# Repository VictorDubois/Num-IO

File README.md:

# Num-IO

Mesa compatible SPI daughter board aimed at being a drop-in remplacement for a 32I/24O Num 1060 board
Also featuring an expansion port with 4 isoSPI lines for panel connectivity

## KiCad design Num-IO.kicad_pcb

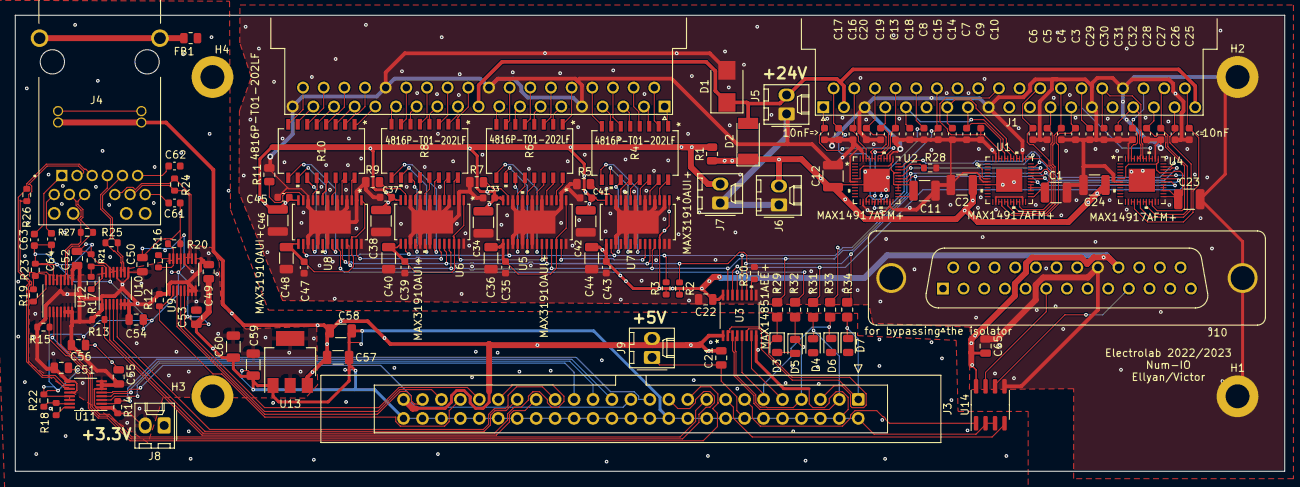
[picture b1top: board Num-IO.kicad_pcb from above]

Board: 4 copper layers, 170.2 x 61.1 mm, 135 parts (0 on the bottom side), 165 nets.

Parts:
C1, C11, C23: 1uF; C_1210_3225Metric
C2, C12, C24: 10uF; C_1210_3225Metric
C3, C4, C5, C6, C7, C8, C9, C10, C13, C14, C15, C16, C17, C18, C19, C20, C25, C26, C27, C28, C29, C30, C31, C32: 10nF; C_0603_1608Metric
C21, C22, C65: 0.1uF; C_0805_2012Metric
C33, C37, C41, C45: 100nF 100V ceramic; C_0603_1608Metric
C34, C38, C42, C46: 10uF 60V ceramic; C_1210_3225Metric
C35, C39, C43, C47: 100nF 10V C; C_0603_1608Metric
C36, C40, C44, C48: 4.7uF 10V lowESR; C_1206_3216Metric
C49, C50, C51, C52, C53, C54, C55, C56: 100nF; C_0805_2012Metric
C57, C58, C59, C60: 10uF; C_1206_3216Metric
C61, C62, C63, C64: <27pF; C_0603_1608Metric
D1: SM6T36A; D_SMB
D2: 1N4007; D_MELF
D3, D4, D5, D6, D7: BZY55B5V6 RBG; D_0805_2012Metric
FB1: FerriteBead; R_0805_2012Metric
H1, H2, H3, H4: MountingHole_Pad; MountingHole_3.2mm_M3_DIN965_Pad
J1: DB37_Female; DSUB-37_Female_Horizontal_P2.77x2.54mm_EdgePinOffset9.40mm
J2: DB37_Male; DSUB-37_Male_Horizontal_P2.77x2.54mm_EdgePinOffset9.40mm
J3: Conn_02x25_Odd_Even; IDC-Header_2x25_P2.54mm_Latch_Vertical
J4: 0826-1X1T-GH-F; BEL_0826-1X1T-GH-F
J5, J6, J7, J8, J9: Conn_01x02_Male; Molex_KK-254_AE-6410-02A_1x02_P2.54mm_Vertical
J10: DB25_Female; DSUB-25_Female_Vertical_P2.77x2.84mm_MountingHoles
R1: 150R; R_0805_2012Metric
R2, R3, R30: 3.3k; R_0603_1608Metric
R4, R6, R8, R10: 4816P-T01-202LF; 4816P
R5, R7, R9, R11: 15k; R_0805_2012Metric
R12, R13, R14, R15: 2kR; R_0603_1608Metric
R16, R17, R18, R19: 2.8kR; R_0603_1608Metric
R20, R21, R22, R23: 1.21kR; R_0603_1608Metric
R24, R25, R26, R27: 120R; R_0603_1608Metric
R28: 100k; R_0603_1608Metric
R29, R31, R32, R33, R34: NC; R_0805_2012Metric_Pad1.20x1.40mm_HandSolder
U1, U2, U4: MAX14917AFM+; MAX14917AFM&plus_
U3: MAX14851AEE+; MAX14851AEE&plus_
U5, U6, U7, U8: MAX31910AUI+; MAX31910AUI&plus_
U9, U10, U11, U12: LTC6820HMS; MSOP-16_3x4.039mm_P0.5mm
U13: AP1117-33; SOT-223-3_TabPin2
U14: HCPL-063A; SOIC-8_3.9x4.9mm_P1.27mm

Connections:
+3V3: C49.1, C50.1, C51.1, C52.1, C53.1, C54.1, C55.1, C56.1, C59.1, C60.1, J8.2, R12.1, R13.1, R14.1, R15.1, U9.1 (EN), U9.6 (VDDS), U9.7 (POL), U9.8 (PHA), U9.9 (VDD), U9.12 (MSTR), U10.1 (EN), U10.6 (VDDS), U10.7 (POL), U10.8 (PHA), U10.9 (VDD), U10.12 (MSTR), U11.1 (EN), U11.6 (VDDS), U11.7 (POL), U11.8 (PHA), U11.9 (VDD), U11.12 (MSTR), U12.1 (EN), U12.6 (VDDS), U12.7 (POL), U12.8 (PHA), U12.9 (VDD), U12.12 (MSTR), U13.2 (VO)
+5VD: C21.2, C57.1, C58.1, J3.49, J4.13 (VC1), J4.14 (VC2), J9.2, U3.1 (VCCA), U13.3 (VI)
+24V: D1.1 (A1), D2.2 (A), J1.2, J1.19, J2.10, J5.2
/*FAULT: R3.2, R33.2, U1.35 (*FAULT), U2.35 (*FAULT), U3.12 (INB2), U4.35 (*FAULT), U5.16 (*FAULT), U6.16 (*FAULT), U7.16 (*FAULT), U8.16 (*FAULT)
/CLK: R29.2, U1.31 (CLK), U2.31 (CLK), U3.15 (OUTB1), U4.31 (CLK), U5.25 (CLK), U6.25 (CLK), U7.25 (CLK), U8.25 (CLK)
/CS: R2.1, R34.2, U1.30 (*CS), U2.30 (*CS), U3.11 (I/OB1), U4.30 (*CS), U5.24 (*CS), U6.24 (*CS), U7.24 (*CS), U8.24 (*CS)
/FPGA Connector/SPI0.*CS: D7.1 (A1), J3.1, R34.1, U3.6 (I/OA1)
/FPGA Connector/SPI0.CLK: D3.1 (A1), J3.5, R29.1, U3.2 (INA1)
/FPGA Connector/SPI0.SDI: D4.1 (A1), J3.3, R31.1, U3.3 (INA2)
/FPGA Connector/SPI0.SDO: D5.1 (A1), J3.7, R32.1, U3.4 (OUTA1)
/FPGA Connector/SPI1.*CS: J3.17, U12.5 (*CS)
/FPGA Connector/SPI1.CLK: J3.21, U12.4 (SCK)
/FPGA Connector/SPI1.SDI: J3.19, R15.2, U12.2 (MOSI)
/FPGA Connector/SPI1.SDO: J3.23, U12.3 (MISO)
/FPGA Connector/SPI2.*CS: J3.25, U11.5 (*CS)
/FPGA Connector/SPI2.CLK: J3.29, U11.4 (SCK)
/FPGA Connector/SPI2.SDI: J3.27, R14.2, U11.2 (MOSI)
/FPGA Connector/SPI2.SDO: J3.31, U11.3 (MISO)
/FPGA Connector/SPI3.*CS: J3.33, U10.5 (*CS)
/FPGA Connector/SPI3.CLK: J3.37, U10.4 (SCK)
/FPGA Connector/SPI3.SDI: J3.35, R13.2, U10.2 (MOSI)
/FPGA Connector/SPI3.SDO: J3.39, U10.3 (MISO)
/FPGA Connector/SPI4.*CS: J3.41, U9.5 (*CS)
/FPGA Connector/SPI4.CLK: J3.45, U9.4 (SCK)
/FPGA Connector/SPI4.SDI: J3.43, R12.2, U9.2 (MOSI)
/FPGA Connector/SPI4.SDO: J3.47, U9.3 (MISO)
/I*FAULT: D6.1 (A1), J3.11, R33.1, U3.5 (OUTA2)
/IADDR: J3.9, U3.7 (I/OA2)
/IMPGA: J3.13, U14.1 (A1)
/IMPGB: J3.15, U14.4 (A2)
/Input connector/IN1: J2.1, R4.1
/Input connector/IN2: J2.20, R4.2
/Input connector/IN3: J2.2, R4.3
/Input connector/IN4: J2.21, R4.4
/Input connector/IN5: J2.3, R4.5
/Input connector/IN6: J2.22, R4.6
/Input connector/IN7: J2.4, R4.7
/Input connector/IN8: J2.23, R4.8
/Input connector/IN9: J2.24, R6.1
/Input connector/IN10: J2.6, R6.2
/Input connector/IN11: J2.25, R6.3
/Input connector/IN12: J2.7, R6.4
/Input connector/IN13: J2.26, R6.5
/Input connector/IN14: J2.8, R6.6
/Input connector/IN15: J2.27, R6.7
/Input connector/IN16: J2.9, R6.8
/Input connector/IN17: J2.29, R8.1
/Input connector/IN18: J2.11, R8.2
/Input connector/IN19: J2.30, R8.3
/Input connector/IN20: J2.12, R8.4
/Input connector/IN21: J2.31, R8.5
/Input connector/IN22: J2.13, R8.6
/Input connector/IN23: J2.32, R8.7
/Input connector/IN24: J2.14, R8.8
/Input connector/IN25: J2.15, R10.1
/Input connector/IN26: J2.34, R10.2
/Input connector/IN27: J2.16, R10.3
/Input connector/IN28: J2.35, R10.4
/Input connector/IN29: J2.17, R10.5
/Input connector/IN30: J2.36, R10.6
/Input connector/IN31: J2.18, R10.7
/Input connector/IN32: J2.37, R10.8
/IsoPWR: C22.1, C43.1, C44.1, C65.2, J10.22, R2.2, R3.1, U3.16 (VCCB), U7.1 (DB0), U7.15 (5VOUT), U7.26 (MODESEL), U14.8 (VCC)
/MPG/MPGA: J10.6, U14.7 (VO1)
/MPG/MPGB: J10.10, U14.6 (VO2)
/RJ45 extension/TRD1+: J4.11 (TRD1+), R24.1, U9.11 (IP)
/RJ45 extension/TRD1-: J4.10 (TRD1-), R24.2, U9.10 (IM)
/RJ45 extension/TRD2+: J4.4 (TRD2+), R25.1, U10.11 (IP)
/RJ45 extension/TRD2-: J4.5 (TRD2-), R25.2, U10.10 (IM)
/RJ45 extension/TRD3+: J4.3 (TRD3+), R26.1, U11.11 (IP)
/RJ45 extension/TRD3-: J4.2 (TRD3-), R26.2, U11.10 (IM)
/RJ45 extension/TRD4+: J4.8 (TRD4+), R27.1, U12.11 (IP)
/RJ45 extension/TRD4-: J4.9 (TRD4-), R27.2, U12.10 (IM)
/SDI: R31.2, U3.14 (OUTB2), U4.32 (SDI)
/SDO: R32.2, U3.13 (INB1), U8.23 (SOUT)
/input channel 1-8/SDO: U5.27 (SIN), U7.23 (SOUT)
/input channel 9-16/5VOUT: C35.1, C36.1, U5.1 (DB0), U5.15 (5VOUT), U5.26 (MODESEL)
/input channel 17-24/5VOUT: C39.1, C40.1, U6.1 (DB0), U6.15 (5VOUT), U6.26 (MODESEL)
/input channel 17-24/SDI: U5.23 (SOUT), U6.27 (SIN)
/input channel 17-24/SDO: U6.23 (SOUT), U8.27 (SIN)
/input channel 25-32/5VOUT: C47.1, C48.1, U8.1 (DB0), U8.15 (5VOUT), U8.26 (MODESEL)
/output channel 1-8/OUT1: C25.1, J1.37, U4.15 (OUT1), U4.16 (OUT1)
/output channel 1-8/OUT2: C26.1, J1.18, U4.17 (OUT2), U4.18 (OUT2)
/output channel 1-8/OUT3: C27.1, J1.36, U4.19 (OUT3), U4.20 (OUT3)
/output channel 1-8/OUT4: C28.1, J1.17, U4.21 (OUT4), U4.22 (OUT4)
/output channel 1-8/OUT5: C32.1, J1.35, U4.45 (OUT5), U4.46 (OUT5)
/output channel 1-8/OUT6: C31.1, J1.16, U4.43 (OUT6), U4.44 (OUT6)
/output channel 1-8/OUT7: C30.1, J1.33, U4.41 (OUT7), U4.42 (OUT7)
/output channel 1-8/OUT8: C29.1, J1.32, U4.39 (OUT8), U4.40 (OUT8)
/output channel 1-8/SDO: U1.32 (SDI), U4.34 (SDO)
/output channel 1-8/VL: C23.1, U4.6 (VL), U4.25 (CRCEN), U4.27 (SPIWD), U4.28 (EN), U4.29 (VA), U4.33 (SYNCH), U4.37 (VL)
/output channel 9-16/OUT1: C3.1, J1.13, U1.15 (OUT1), U1.16 (OUT1)
/output channel 9-16/OUT2: C4.1, J1.31, U1.17 (OUT2), U1.18 (OUT2)
/output channel 9-16/OUT3: C5.1, J1.12, U1.19 (OUT3), U1.20 (OUT3)
/output channel 9-16/OUT4: C6.1, J1.30, U1.21 (OUT4), U1.22 (OUT4)
/output channel 9-16/OUT5: C10.1, J1.28, U1.45 (OUT5), U1.46 (OUT5)
/output channel 9-16/OUT6: C9.1, J1.8, U1.43 (OUT6), U1.44 (OUT6)
/output channel 9-16/OUT7: C8.1, J1.5, U1.41 (OUT7), U1.42 (OUT7)
/output channel 9-16/OUT8: C7.1, J1.7, U1.39 (OUT8), U1.40 (OUT8)
/output channel 9-16/VL: C1.1, U1.6 (VL), U1.25 (CRCEN), U1.27 (SPIWD), U1.28 (EN), U1.29 (VA), U1.33 (SYNCH), U1.37 (VL)
/output channel 17-24/OUT1: C13.1, J1.4, U2.15 (OUT1), U2.16 (OUT1)
/output channel 17-24/OUT2: C14.1, J1.25, U2.17 (OUT2), U2.18 (OUT2)
/output channel 17-24/OUT3: C15.1, J1.24, U2.19 (OUT3), U2.20 (OUT3)
/output channel 17-24/OUT4: C16.1, J1.20, U2.21 (OUT4), U2.22 (OUT4)
/output channel 17-24/OUT5: C20.1, J1.21, U2.45 (OUT5), U2.46 (OUT5)
/output channel 17-24/OUT6: C19.1, J1.22, U2.43 (OUT6), U2.44 (OUT6)
/output channel 17-24/OUT7: C18.1, J1.23, U2.41 (OUT7), U2.42 (OUT7)
/output channel 17-24/OUT8: C17.1, J1.1, U2.39 (OUT8), U2.40 (OUT8)
/output channel 17-24/SDI: U1.34 (SDO), U2.32 (SDI)
/output channel 17-24/SDO: R28.2, U2.34 (SDO)
/output channel 17-24/VL: C11.1, U2.6 (VL), U2.25 (CRCEN), U2.27 (SPIWD), U2.28 (EN), U2.29 (VA), U2.33 (SYNCH), U2.37 (VL)
GNDD: C21.1, C49.2, C50.2, C51.2, C52.2, C53.2, C54.2, C55.2, C56.2, C57.2, C58.2, C59.2, C60.2, C61.1, C62.1, C63.1, C64.1, D3.2 (A2), D4.2 (A2), D5.2 (A2), D6.2 (A2), D7.2 (A2), FB1.1, J3.2, J3.4, J3.6, J3.8, J3.10, J3.12, J3.14, J3.16, J3.18, J3.20, J3.22, J3.24, J3.26, J3.28, J3.30, J3.32, J3.34, J3.36, J3.38, J3.40, J3.42, J3.44, J3.46, J3.48, J3.50, J4.15 (VC3), J4.16 (VC4), J8.1, J9.1, R20.2, R21.2, R22.2, R23.2, U3.8 (GNDA), U9.13 (SLOW), U9.14 (GND), U10.13 (SLOW), U10.14 (GND), U11.13 (SLOW), U11.14 (GND), U12.13 (SLOW), U12.14 (GND), U13.1 (GND), U14.2 (C1), U14.3 (C2)
GNDPWR: C1.2, C2.2, C3.2, C4.2, C5.2, C6.2, C7.2, C8.2, C9.2, C10.2, C11.2, C12.2, C13.2, C14.2, C15.2, C16.2, C17.2, C18.2, C19.2, C20.2, C22.2, C23.2, C24.2, C25.2, C26.2, C27.2, C28.2, C29.2, C30.2, C31.2, C32.2, C33.2, C34.2, C35.2, C36.2, C37.2, C38.2, C39.2, C40.2, C41.2, C42.2, C43.2, C44.2, C45.2, C46.2, C47.2, C48.2, C65.1, D1.2 (A2), H1.1, H2.1, J1.3, J1.9, J1.14, J1.34, J2.5, J2.19, J2.28, J2.33, J5.1, J6.1, J7.1, J10.0 (PAD), J10.21, R5.1, R7.1, R9.1, R11.1, R28.1, R30.2, U1.7 (SYNCHWD), U1.14 (GND), U1.23 (GND), U1.38 (GND), U1.47 (GND), U2.7 (SYNCHWD), U2.14 (GND), U2.23 (GND), U2.38 (GND), U2.47 (GND), U3.9 (GNDB), U4.7 (SYNCHWD), U4.14 (GND), U4.23 (GND), U4.38 (GND), U4.47 (GND), U5.2 (DB1), U5.4 (RT1), U5.6 (RT2), U5.8 (RT3), U5.10 (RT4), U5.12 (RT5), U5.17 (RT6), U5.19 (RT7), U5.21 (RT8), U5.28 (GND), U5.EPAD, U6.2 (DB1), U6.4 (RT1), U6.6 (RT2), U6.8 (RT3), U6.10 (RT4), U6.12 (RT5), U6.17 (RT6), U6.19 (RT7), U6.21 (RT8), U6.28 (GND), U6.EPAD, U7.2 (DB1), U7.4 (RT1), U7.6 (RT2), U7.8 (RT3), U7.10 (RT4), U7.12 (RT5), U7.17 (RT6), U7.19 (RT7), U7.21 (RT8), U7.27 (SIN), U7.28 (GND), U7.EPAD, U8.2 (DB1), U8.4 (RT1), U8.6 (RT2), U8.8 (RT3), U8.10 (RT4), U8.12 (RT5), U8.17 (RT6), U8.19 (RT7), U8.21 (RT8), U8.28 (GND), U8.EPAD, U14.5 (GND)
INPWR: C33.1, C34.1, C37.1, C38.1, C41.1, C42.1, C45.1, C46.1, J7.2, R1.2, U5.14 (VCC24V), U6.14 (VCC24V), U7.14 (VCC24V), U8.14 (VCC24V)
unnamed: C61.2, J4.12 (TRCT1)
unnamed: C62.2, J4.6 (TRCT2)
unnamed: C63.2, J4.1 (TRCT3)
unnamed: C64.2, J4.7 (TRCT4)
unnamed: FB1.2, J4.S1 (SHIELD), J4.S2 (SHIELD)
unnamed: R4.9, U7.22 (IN8)
unnamed: R4.10, U7.20 (IN7)
unnamed: R4.11, U7.18 (IN6)
unnamed: R4.12, U7.11 (IN5)
unnamed: R4.13, U7.9 (IN4)
unnamed: R4.14, U7.7 (IN3)
unnamed: R4.15, U7.5 (IN2)
unnamed: R4.16, U7.3 (IN1)
unnamed: R5.2, U7.13 (RIREF)
unnamed: R6.9, U5.22 (IN8)
unnamed: R6.10, U5.20 (IN7)
unnamed: R6.11, U5.18 (IN6)
unnamed: R6.12, U5.11 (IN5)
unnamed: R6.13, U5.9 (IN4)
unnamed: R6.14, U5.7 (IN3)
unnamed: R6.15, U5.5 (IN2)
unnamed: R6.16, U5.3 (IN1)
unnamed: R7.2, U5.13 (RIREF)
unnamed: R8.9, U6.22 (IN8)
unnamed: R8.10, U6.20 (IN7)
unnamed: R8.11, U6.18 (IN6)
unnamed: R8.12, U6.11 (IN5)
unnamed: R8.13, U6.9 (IN4)
unnamed: R8.14, U6.7 (IN3)
unnamed: R8.15, U6.5 (IN2)
unnamed: R8.16, U6.3 (IN1)
unnamed: R9.2, U6.13 (RIREF)
unnamed: R10.9, U8.22 (IN8)
unnamed: R10.10, U8.20 (IN7)
unnamed: R10.11, U8.18 (IN6)
unnamed: R10.12, U8.11 (IN5)
unnamed: R10.13, U8.9 (IN4)
unnamed: R10.14, U8.7 (IN3)
unnamed: R10.15, U8.5 (IN2)
unnamed: R10.16, U8.3 (IN1)
unnamed: R11.2, U8.13 (RIREF)
unnamed: R16.1, R20.1, U9.15 (ICMP)
unnamed: R16.2, U9.16 (IBIAS)
unnamed: R17.1, R21.1, U10.15 (ICMP)
unnamed: R17.2, U10.16 (IBIAS)
unnamed: R18.1, R22.1, U11.15 (ICMP)
unnamed: R18.2, U11.16 (IBIAS)
unnamed: R19.1, R23.1, U12.15 (ICMP)
unnamed: R19.2, U12.16 (IBIAS)
unnamed: R30.1, U3.10 (I/OB2)
OUTPWR: C2.1, C12.1, C24.1, D2.1 (K), J6.2, R1.1, U1.8 (VDD), U1.49 (EPAD), U2.8 (VDD), U2.49 (EPAD), U4.8 (VDD), U4.49 (EPAD)

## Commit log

2022-08-16 Common power stage for field IO
2022-08-17 Further simplifying the schematics
2022-12-27 add Maxime industrial IO files
2022-12-27 fix outlines of Maxim industrial IO
2022-12-27 fix DRC errors
2022-12-28 routing stuff
2022-12-28 Basic routing done, cheating a bit on the diff + add holes (to be positionned)
2022-12-28 before switching packaging
2022-12-28 change package QFN => MSOP
2022-12-28 add missing LDO for 3.3V
2023-01-01 fix a few warnings
2023-01-03 fix most errors/warnings
2023-01-03 add KK connectors for power (check voltage or bypass)
2023-01-10 add resistances for bypassing the isolator
2023-01-10 add MPGA and MPGB on a DB25 (isolated)
2023-01-12 add condo for MPG isolator + small rerouting pair diff
2023-01-12 add vias
2023-01-14 add zeners in the meantime, if the SPI isolator is delayed
2023-01-14 4 couches
2023-01-14 tuning
2023-01-16 J'ai oublié de commiter ça, mais j'ai recommencé sur mon autre PC
2023-01-16 add logo + move M3 holes
2023-01-16 move MPG to dedicated file
2023-01-16 remove 5V (now 3.3V) + tuning
2023-01-18 fix warnings
2023-01-19 add mounting holes for stencil (not sure if correct) + specify where to put prod number ("JLCJLCJLCJLC")
2023-01-31 start BOM
2023-02-04 Farnell command - missing db37 male connector
2023-03-04 fixes after V1
    4 resistors for input power
    disable CRCEN

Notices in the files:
parts and their libraries:
Copyright 2021 Accelerated Designs. All rights reserved.
